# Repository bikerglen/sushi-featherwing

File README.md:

# sushi-featherwing

The Sushi FeatherWing is for use with the Adafruit HUZZAH ESP32 Feather and the slim 640x48 LCDs found in the various dragon, wizard, and fairy magic wand toys.

Boards available at OSH Park: https://oshpark.com/shared_projects/a6137iE9

The required 22-pin, 0.5mm pitch FFC connector is Amphenol part # SFV22R-2STE1HLF, Digi-Key part # 609-4319-1-ND.

I picked Vled and R1 to limit the backlight current to 5mA on my module.

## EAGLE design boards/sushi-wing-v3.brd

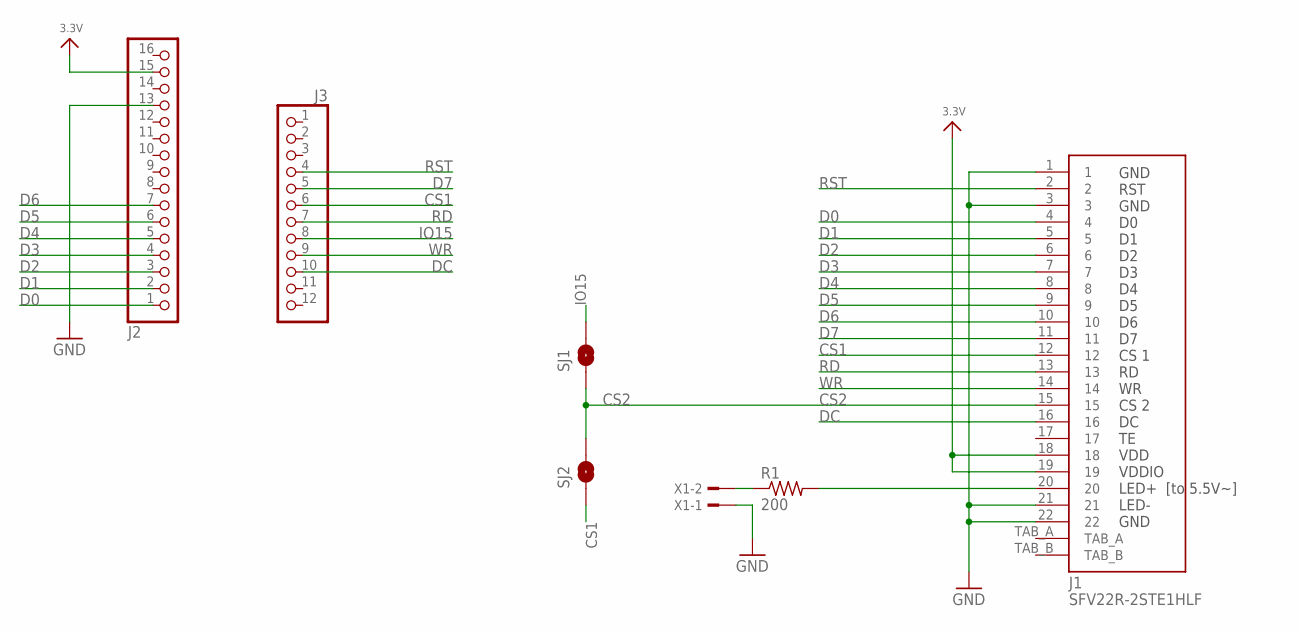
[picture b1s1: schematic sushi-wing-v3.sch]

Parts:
J1: SFV22R-2STE1HLF
J2: HEADER-1X16_MIN; 1X16_ROUND_MIN
J3: HEADER-1X12_MIN; 1X12_ROUND_MIN
R1: 200; R1206
SJ1, SJ2: SOLDERJUMPERNO; SJ_2S-NO
X1: TSW-102-02-S-S-RA

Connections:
3.3V: J1.18, J1.19, J2.15
CS1: J1.12, J3.6, SJ2.1
CS2: J1.15, SJ1.1, SJ2.2
D0: J1.4, J2.1
D1: J1.5, J2.2
D2: J1.6, J2.3
D3: J1.7, J2.4
D4: J1.8, J2.5
D5: J1.9, J2.6
D6: J1.10, J2.7
D7: J1.11, J3.5
DC: J1.16, J3.10
GND: J1.1, J1.3, J1.21, J1.22, J2.13, X1.1
IO15: J3.8, SJ1.2
unnamed: R1.1, X1.2
unnamed: J1.20, R1.2
RD: J1.13, J3.7
RST: J1.2, J3.4
WR: J1.14, J3.9

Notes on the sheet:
GND RST GND D0 D1 D2 D3 D4 D5 D6 D7 CS 1 RD WR CS 2 DC TE VDD VDDIO LED+ [to 5.5V~] LED- GND

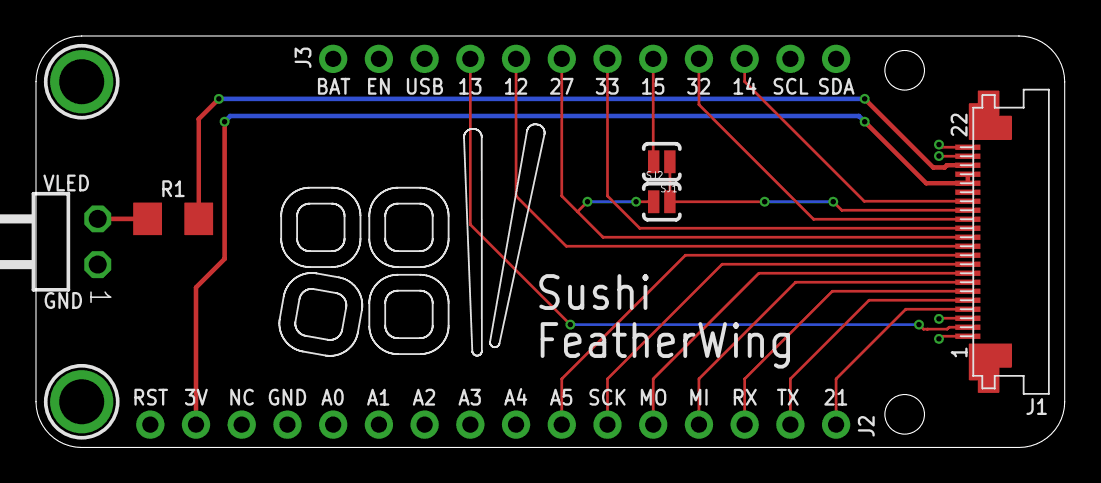
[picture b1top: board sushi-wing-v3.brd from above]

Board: 2 copper layers, 57.1 x 22.9 mm, 9 parts (0 on the bottom side), 19 nets.

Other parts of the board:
U$31, U$32: MOUNTINGHOLE2.5; MOUNTINGHOLE_2.5_PLATED

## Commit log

2021-02-24 initial checkin
2021-02-24 added gerbers
2021-02-24 add link to board at osh park
2021-02-25 add FFC connector part number
2021-02-25 added note about backlight current

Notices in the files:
parts and their libraries:
microbuilder: This work is placed in the public domain, and may be freely used for commercial and non-commercial work with the following conditions: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
